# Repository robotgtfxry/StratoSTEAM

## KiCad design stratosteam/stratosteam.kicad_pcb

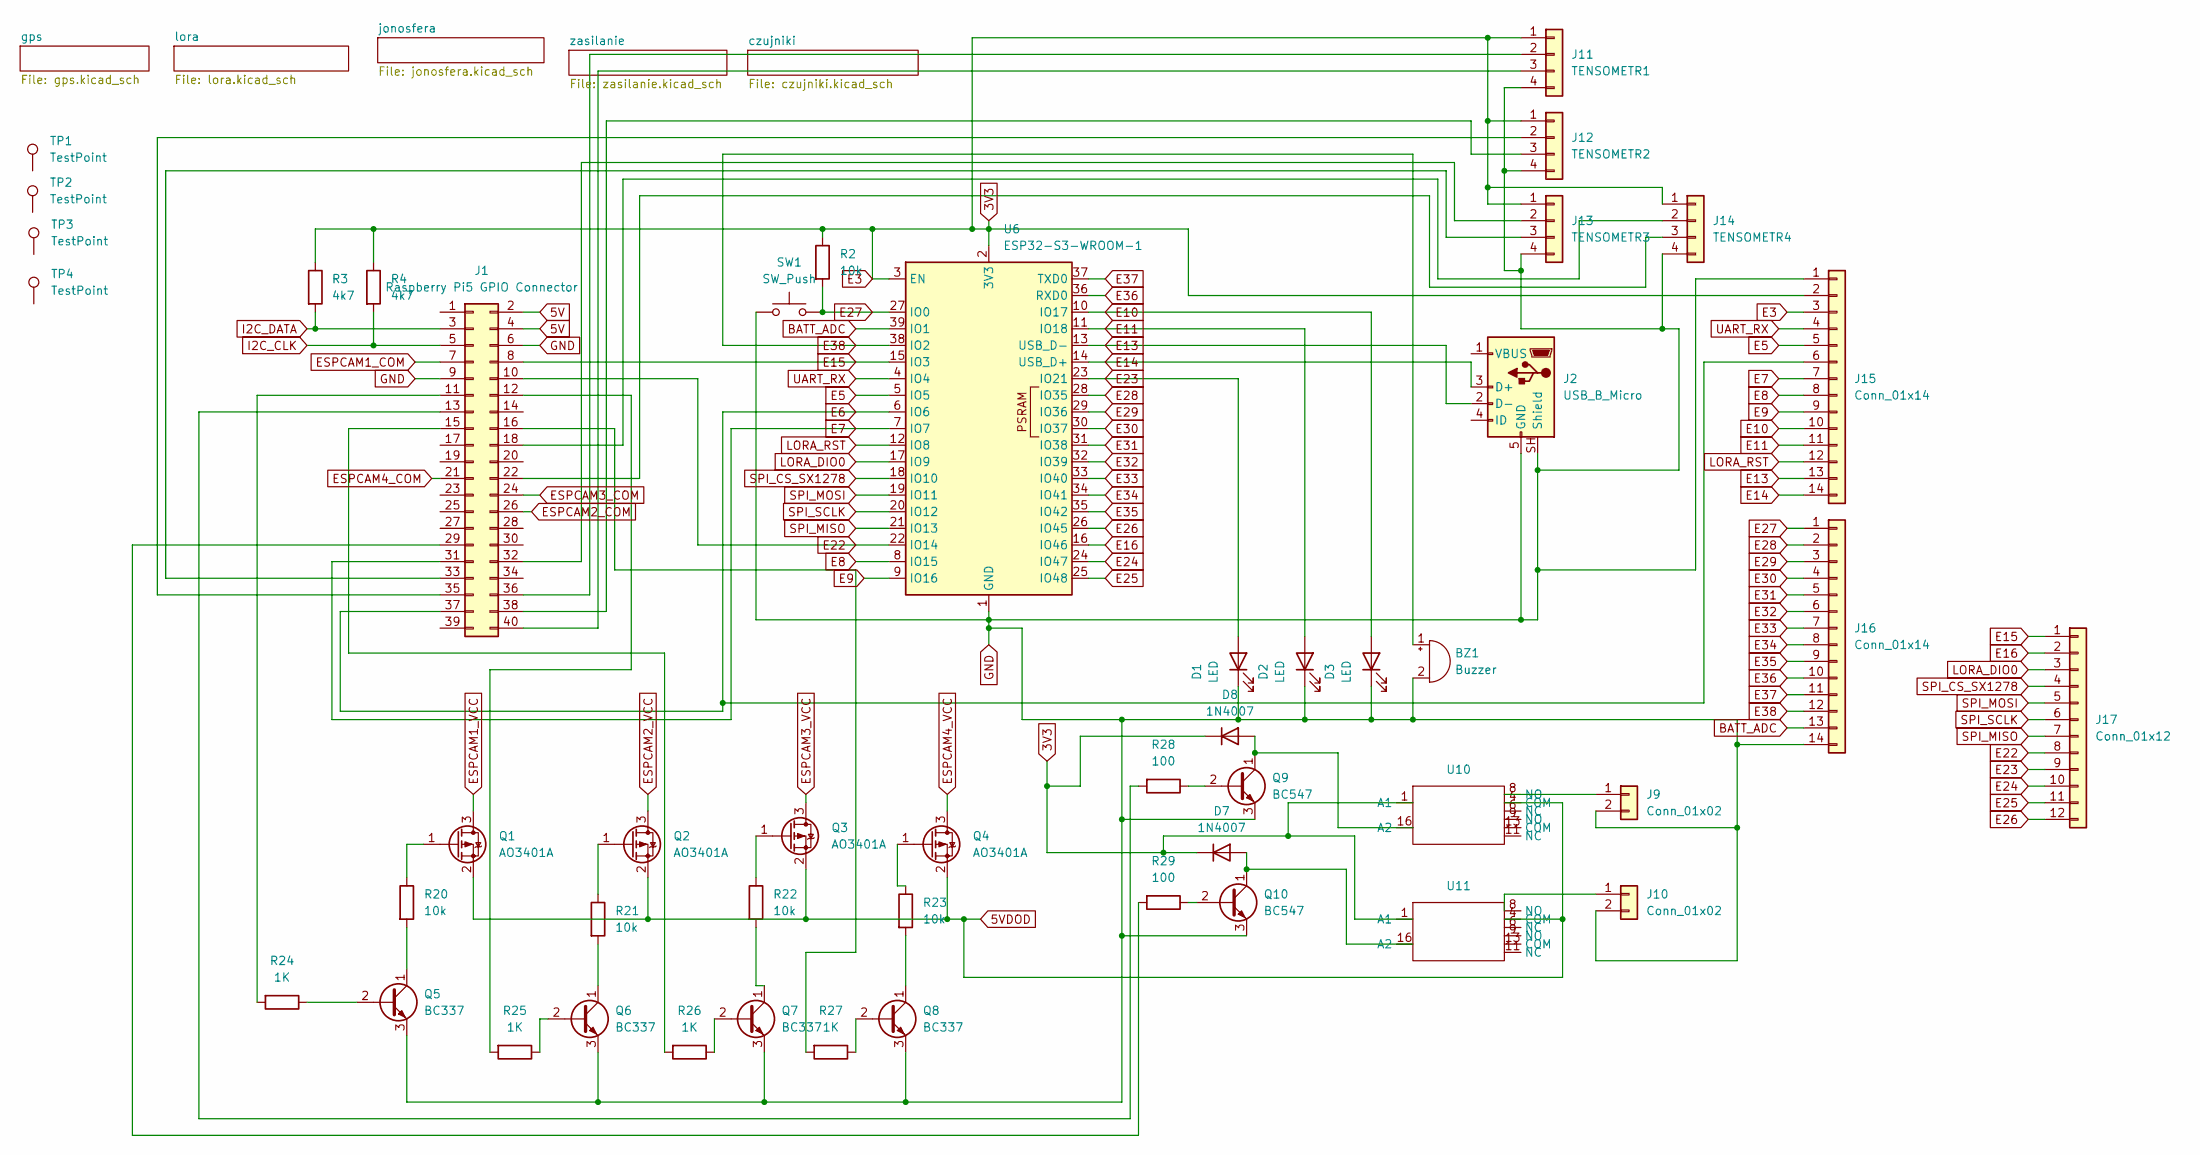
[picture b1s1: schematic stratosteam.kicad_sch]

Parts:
BZ1: Buzzer; Buzzer_12x9.5RM7.6
D1, D2, D3: LED; LED_D3.0mm
D7, D8: 1N4007; D_DO-41_SOD81_P10.16mm_Horizontal
J1: Raspberry Pi5 GPIO Connector; PinHeader_2x20_P2.54mm_Vertical
J2: USB_B_Micro; USB_Micro-B_Molex-105017-0001
J9, J10: Conn_01x02; JST_XH_B2B-XH-AM_1x02_P2.50mm_Vertical
J11: TENSOMETR1; JST_XH_B4B-XH-AM_1x04_P2.50mm_Vertical
J12: TENSOMETR2; JST_XH_B4B-XH-AM_1x04_P2.50mm_Vertical
J13: TENSOMETR3; JST_XH_B4B-XH-AM_1x04_P2.50mm_Vertical
J14: TENSOMETR4; JST_XH_B4B-XH-AM_1x04_P2.50mm_Vertical
J15, J16: Conn_01x14; PinHeader_1x14_P2.54mm_Vertical
J17: Conn_01x12; PinHeader_1x12_P2.54mm_Vertical
Q1, Q2, Q3, Q4: AO3401A; SOT-23_Handsoldering
Q5, Q6, Q7, Q8: BC337; TO-92_Inline
Q9, Q10: BC547; TO-92_Inline
R2: 10k; R_Axial_DIN0207_L6.3mm_D2.5mm_P15.24mm_Horizontal
R3, R4: 4k7; R_Axial_DIN0207_L6.3mm_D2.5mm_P15.24mm_Horizontal
R20, R21, R22, R23: 10k; R_0805_2012Metric_Pad1.20x1.40mm_HandSolder
R24, R25, R26, R27: 1K; R_0805_2012Metric_Pad1.20x1.40mm_HandSolder
R28, R29: 100; R_0805_2012Metric_Pad1.20x1.40mm_HandSolder
SW1: SW_Push; SW_DIP_SPSTx01_Slide_9.78x4.72mm_W7.62mm_P2.54mm
TP1, TP2, TP3, TP4: TestPoint; TestPoint_Loop_D3.80mm_Drill2.8mm
U6: ESP32-S3-WROOM-1
U10, U11: HJR1-2C SERIES

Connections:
3V3: D7.1 (K), D8.1 (K), J11.1, J12.1, J13.1, J14.1, J15.2, J15.3, R2.1, R3.1, R4.1, U6.2 (3V3), U6.3 (EN), U10.1 (A1), U11.1 (A1); also elsewhere on the board
5V: J1.2, J1.4; also elsewhere on the board
5VDOD: Q1.2 (S), Q2.2 (S), Q3.2 (S), Q4.2 (S), U10.4 (COM), U11.4 (COM); also elsewhere on the board
BAT-: BZ1.2 (-), D1.1 (K), D2.1 (K), D3.1 (K), J1.6, J1.9, J2.5 (GND), J2.SH (Shield), J9.2, J10.2, J11.4, J12.4, J13.4, J14.4, J15.1, J16.14, Q5.3 (E), Q6.3 (E), Q7.3 (E), Q8.3 (E), Q9.3 (E), Q10.3 (E), SW1.1, U6.1 (GND), U6.40 (GND), U6.41 (GND); also elsewhere on the board
BATT_ADC: J16.13, U6.39 (IO1); also elsewhere on the board
E5: J15.5, U6.5 (IO5)
E6: J1.37, J15.6, U6.6 (IO6); also elsewhere on the board
E7: J1.31, J15.7, U6.7 (IO7); also elsewhere on the board
E8: J15.8, U6.8 (IO15)
E9: J15.9, U6.9 (IO16)
E10: D3.2 (A), J15.10, U6.10 (IO17)
E11: D2.2 (A), J15.11, U6.11 (IO18)
E13: J2.2 (D-), J15.13, U6.13 (USB_D-)
E14: J2.3 (D+), J15.14, U6.14 (USB_D+)
E15: J1.8, J17.1, U6.15 (IO3); also elsewhere on the board
E16: J17.2, U6.16 (IO46)
E22: J1.10, J17.8, U6.22 (IO14); also elsewhere on the board
E23: D1.2 (A), J17.9, U6.23 (IO21)
E24: J17.10, U6.24 (IO47)
E25: J17.11, U6.25 (IO48)
E26: J17.12, U6.26 (IO45)
E27: J16.1, R2.2, SW1.2, U6.27 (IO0)
E28: J16.2, U6.28 (IO35)
E29: J16.3, U6.29 (IO36)
E30: J16.4, U6.30 (IO37)
E31: J16.5, U6.31 (IO38)
E32: J16.6, U6.32 (IO39)
E33: J16.7, U6.33 (IO40)
E34: J16.8, U6.34 (IO41)
E35: J16.9, U6.35 (IO42)
E36: J16.10, U6.36 (RXD0)
E37: J16.11, U6.37 (TXD0)
E38: BZ1.1 (+), J16.12, U6.38 (IO2)
ESPCAM1_COM: J1.7; also elsewhere on the board
ESPCAM1_VCC: Q1.3 (D); also elsewhere on the board
ESPCAM2_COM: J1.26; also elsewhere on the board
ESPCAM2_VCC: Q2.3 (D); also elsewhere on the board
ESPCAM3_COM: J1.24; also elsewhere on the board
ESPCAM3_VCC: Q3.3 (D); also elsewhere on the board
ESPCAM4_COM: J1.21; also elsewhere on the board
ESPCAM4_VCC: Q4.3 (D); also elsewhere on the board
I2C_CLK: J1.5, R4.2; also elsewhere on the board
I2C_DATA: J1.3, R3.2; also elsewhere on the board
LORA_DIO0: J17.3, U6.17 (IO9); also elsewhere on the board
LORA_RST: J15.12, U6.12 (IO8); also elsewhere on the board
unnamed: D7.2 (A), Q10.1 (C), U11.16 (A2)
unnamed: D8.2 (A), Q9.1 (C), U10.16 (A2)
unnamed 55: J1.11, R24.2; also elsewhere on the board
unnamed 56: J1.12, R25.2; also elsewhere on the board
unnamed 57: J1.13, R28.2; also elsewhere on the board
unnamed 58: J1.15, R26.2; also elsewhere on the board
unnamed 59: J1.16, R27.2; also elsewhere on the board
unnamed 60: J1.18, J14.2; also elsewhere on the board
unnamed 61: J1.22, J14.3; also elsewhere on the board
unnamed 62: J1.29, R29.2; also elsewhere on the board
unnamed 63: J1.32, J13.2; also elsewhere on the board
unnamed 64: J1.33, J13.3; also elsewhere on the board
unnamed 65: J1.35, J12.2; also elsewhere on the board
unnamed 66: J1.36, J11.2; also elsewhere on the board
unnamed 67: J1.38, J12.3; also elsewhere on the board
unnamed 68: J1.40, J11.3; also elsewhere on the board
unnamed: J9.1, U10.8 (NO)
unnamed: J10.1, U11.8 (NO)
unnamed: Q1.1 (G), R20.1
unnamed: Q2.1 (G), R21.1
unnamed: Q3.1 (G), R22.1
unnamed: Q4.1 (G), R23.1
unnamed: Q5.2 (B), R24.1
unnamed: Q5.1 (C), R20.2
unnamed: Q6.2 (B), R25.1
unnamed: Q6.1 (C), R21.2
unnamed: Q7.2 (B), R26.1
unnamed: Q7.1 (C), R22.2
unnamed: Q8.2 (B), R27.1
unnamed: Q8.1 (C), R23.2
unnamed: Q9.2 (B), R28.1
unnamed: Q10.2 (B), R29.1
SPI_CS_SX1278: J17.4, U6.18 (IO10); also elsewhere on the board
SPI_MISO: J17.7, U6.21 (IO13); also elsewhere on the board
SPI_MOSI: J17.5, U6.19 (IO11); also elsewhere on the board
SPI_SCLK: J17.6, U6.20 (IO12); also elsewhere on the board
UART_RX: J15.4, U6.4 (IO4); also elsewhere on the board

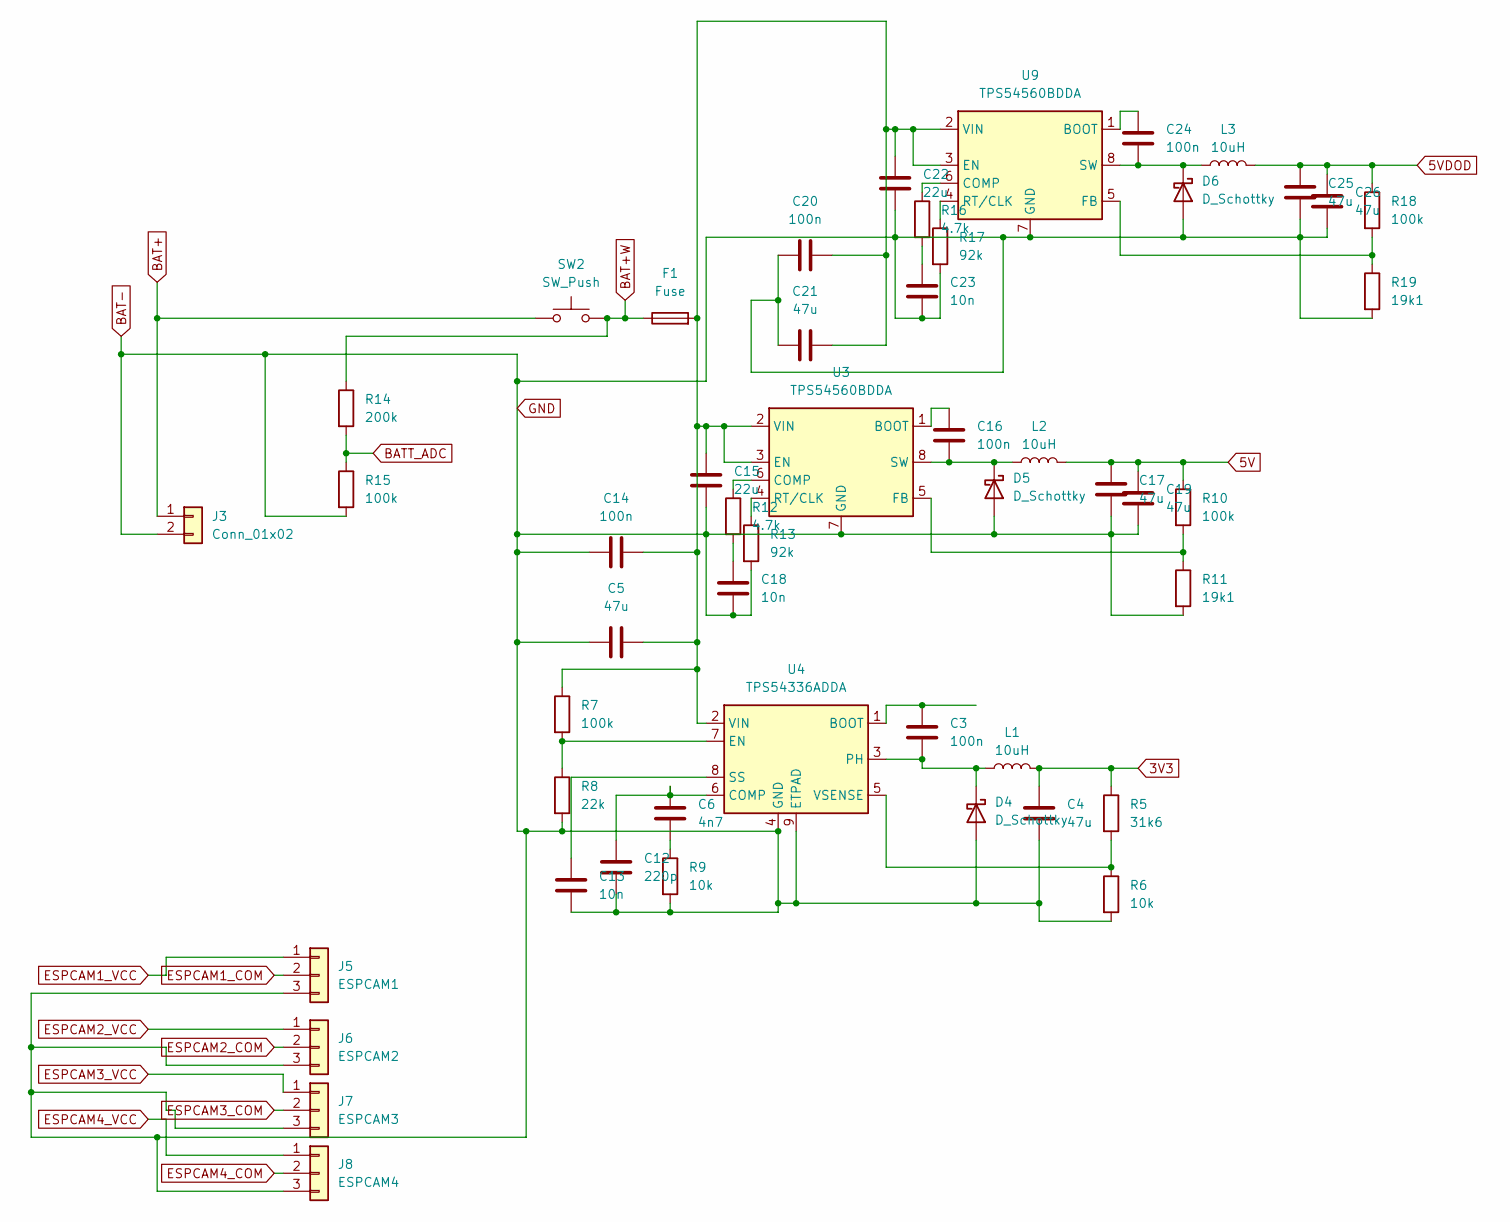
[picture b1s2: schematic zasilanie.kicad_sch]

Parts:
C3, C14, C16, C20, C24: 100n; C_0603_1608Metric_Pad1.08x0.95mm_HandSolder
C4, C17, C19, C25, C26: 47u; C_1210_3225Metric_Pad1.33x2.70mm_HandSolder
C5, C21: 47u; C_1206_3216Metric_Pad1.33x1.80mm_HandSolder
C6: 4n7; C_0603_1608Metric_Pad1.08x0.95mm_HandSolder
C12: 220p; C_0603_1608Metric_Pad1.08x0.95mm_HandSolder
C13, C18, C23: 10n; C_0603_1608Metric_Pad1.08x0.95mm_HandSolder
C15, C22: 22u; C_1206_3216Metric_Pad1.33x1.80mm_HandSolder
D4, D5, D6: D_Schottky; D_SMA
F1: Fuse; Fuseholder_Blade_ATO_Littelfuse_Pudenz_2_Pin
J3: Conn_01x02; SolderWire-2.5sqmm_1x02_P8.8mm_D2.4mm_OD4.4mm
J5: ESPCAM1; JST_XH_B3B-XH-A_1x03_P2.50mm_Vertical
J6: ESPCAM2; JST_XH_B3B-XH-A_1x03_P2.50mm_Vertical
J7: ESPCAM3; JST_XH_B3B-XH-A_1x03_P2.50mm_Vertical
J8: ESPCAM4; JST_XH_B3B-XH-A_1x03_P2.50mm_Vertical
L1, L2, L3: 10uH; L_12x12mm_H4.5mm
R5: 31k6; C_0603_1608Metric_Pad1.08x0.95mm_HandSolder
R6, R9: 10k; C_0603_1608Metric_Pad1.08x0.95mm_HandSolder
R7, R10, R15, R18: 100k; C_0603_1608Metric_Pad1.08x0.95mm_HandSolder
R8: 22k; C_0603_1608Metric_Pad1.08x0.95mm_HandSolder
R11, R19: 19k1; C_0603_1608Metric_Pad1.08x0.95mm_HandSolder
R12, R16: 4.7k; C_0603_1608Metric_Pad1.08x0.95mm_HandSolder
R13, R17: 92k; C_0603_1608Metric_Pad1.08x0.95mm_HandSolder
R14: 200k; C_0603_1608Metric_Pad1.08x0.95mm_HandSolder
SW2: SW_Push; SW_DIP_SPSTx01_Slide_9.78x4.72mm_W7.62mm_P2.54mm
U3, U9: TPS54560BDDA; Texas_R-PDSO-G8_EP2.95x4.9mm_Mask2.4x3.1mm_ThermalVias
U4: TPS54336ADDA; TI_SO-PowerPAD-8_ThermalVias

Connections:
3V3: C4.1, L1.2, R5.1; also elsewhere on the board
5V: C17.1, C19.1, L2.2, R10.1; also elsewhere on the board
5VDOD: C25.1, C26.1, L3.2, R18.1; also elsewhere on the board
BAT+: J3.1, SW2.1
BAT+W: F1.1, R14.1, SW2.2; also elsewhere on the board
BAT-: C4.2, C5.2, C12.2, C13.2, C14.1, C15.2, C17.2, C18.2, C19.2, C20.1, C21.2, C22.2, C23.2, C25.2, C26.2, D4.2 (A), D5.2 (A), D6.2 (A), J3.2, J5.3, J6.3, J7.3, J8.3, R6.2, R8.2, R9.2, R11.2, R13.2, R15.2, R17.2, R19.2, U3.7 (GND), U3.9 (GND), U4.4 (GND), U4.9 (ETPAD), U9.7 (GND), U9.9 (GND); also elsewhere on the board
BATT_ADC: R14.2, R15.1; also elsewhere on the board
ESPCAM1_COM: J5.2; also elsewhere on the board
ESPCAM1_VCC: J5.1; also elsewhere on the board
ESPCAM2_COM: J6.2; also elsewhere on the board
ESPCAM2_VCC: J6.1; also elsewhere on the board
ESPCAM3_COM: J7.2; also elsewhere on the board
ESPCAM3_VCC: J7.1; also elsewhere on the board
ESPCAM4_COM: J8.2; also elsewhere on the board
ESPCAM4_VCC: J8.1; also elsewhere on the board
unnamed: C6.2, R9.1
unnamed: C18.1, R12.2
unnamed: C23.1, R16.2
unnamed: C3.2, D4.1 (K), L1.1, U4.3 (PH)
unnamed: C16.2, D5.1 (K), L2.1, U3.8 (SW)
unnamed: C24.2, D6.1 (K), L3.1, U9.8 (SW)
unnamed: C16.1, U3.1 (BOOT)
unnamed: R12.1, U3.6 (COMP)
unnamed: C5.1, C14.2, C15.1, C20.2, C21.1, C22.1, F1.2, R7.1, U3.2 (VIN), U3.3 (EN), U4.2 (VIN), U9.2 (VIN), U9.3 (EN)
unnamed: R10.2, R11.1, U3.5 (FB)
unnamed: R13.1, U3.4 (RT/CLK)
unnamed: C3.1, U4.1 (BOOT)
unnamed: C6.1, C12.1, U4.6 (COMP)
unnamed: R7.2, R8.1, U4.7 (EN)
unnamed: C13.1, U4.8 (SS)
unnamed: R5.2, R6.1, U4.5 (VSENSE)
unnamed: C24.1, U9.1 (BOOT)
unnamed: R16.1, U9.6 (COMP)
unnamed: R18.2, R19.1, U9.5 (FB)
unnamed: R17.1, U9.4 (RT/CLK)

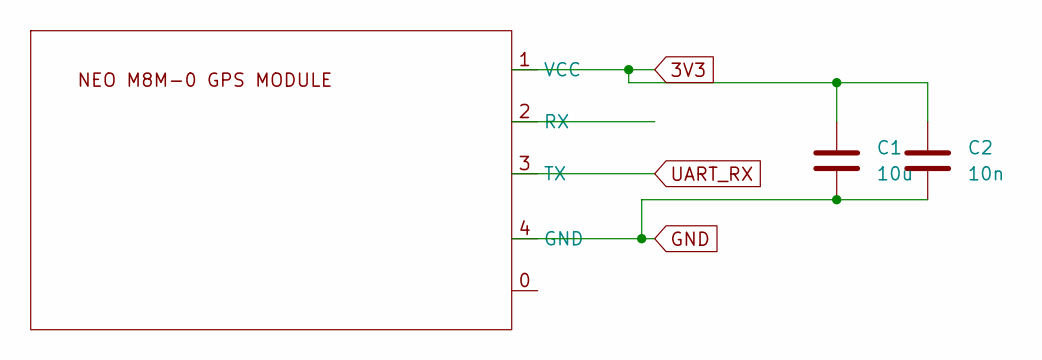
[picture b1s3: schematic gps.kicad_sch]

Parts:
C1: 10u; C_1210_3225Metric_Pad1.33x2.70mm_HandSolder
C2: 10n; C_1210_3225Metric_Pad1.33x2.70mm_HandSolder
U1: Untitled

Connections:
3V3: C1.1, C2.1, U1.1 (VCC); also elsewhere on the board
BAT-: C1.2, C2.2, U1.4 (GND); also elsewhere on the board
UART_RX: U1.3 (TX); also elsewhere on the board

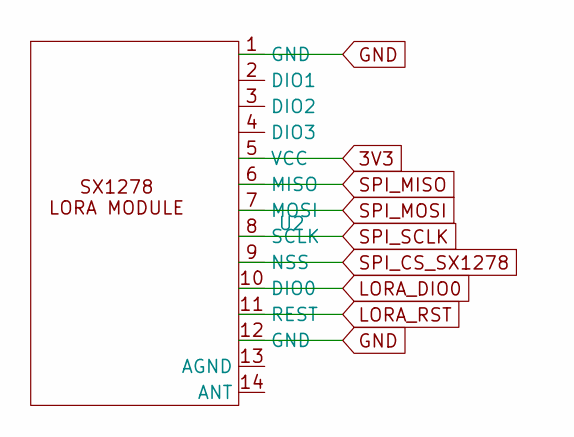
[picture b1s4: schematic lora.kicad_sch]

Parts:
U2: SX1278 MODULE

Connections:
3V3: U2.5 (VCC); also elsewhere on the board
BAT-: U2.1 (GND), U2.12 (GND); also elsewhere on the board
LORA_DIO0: U2.10 (DIO0); also elsewhere on the board
LORA_RST: U2.11 (REST); also elsewhere on the board
SPI_CS_SX1278: U2.9 (NSS); also elsewhere on the board
SPI_MISO: U2.6 (MISO); also elsewhere on the board
SPI_MOSI: U2.7 (MOSI); also elsewhere on the board
SPI_SCLK: U2.8 (SCLK); also elsewhere on the board

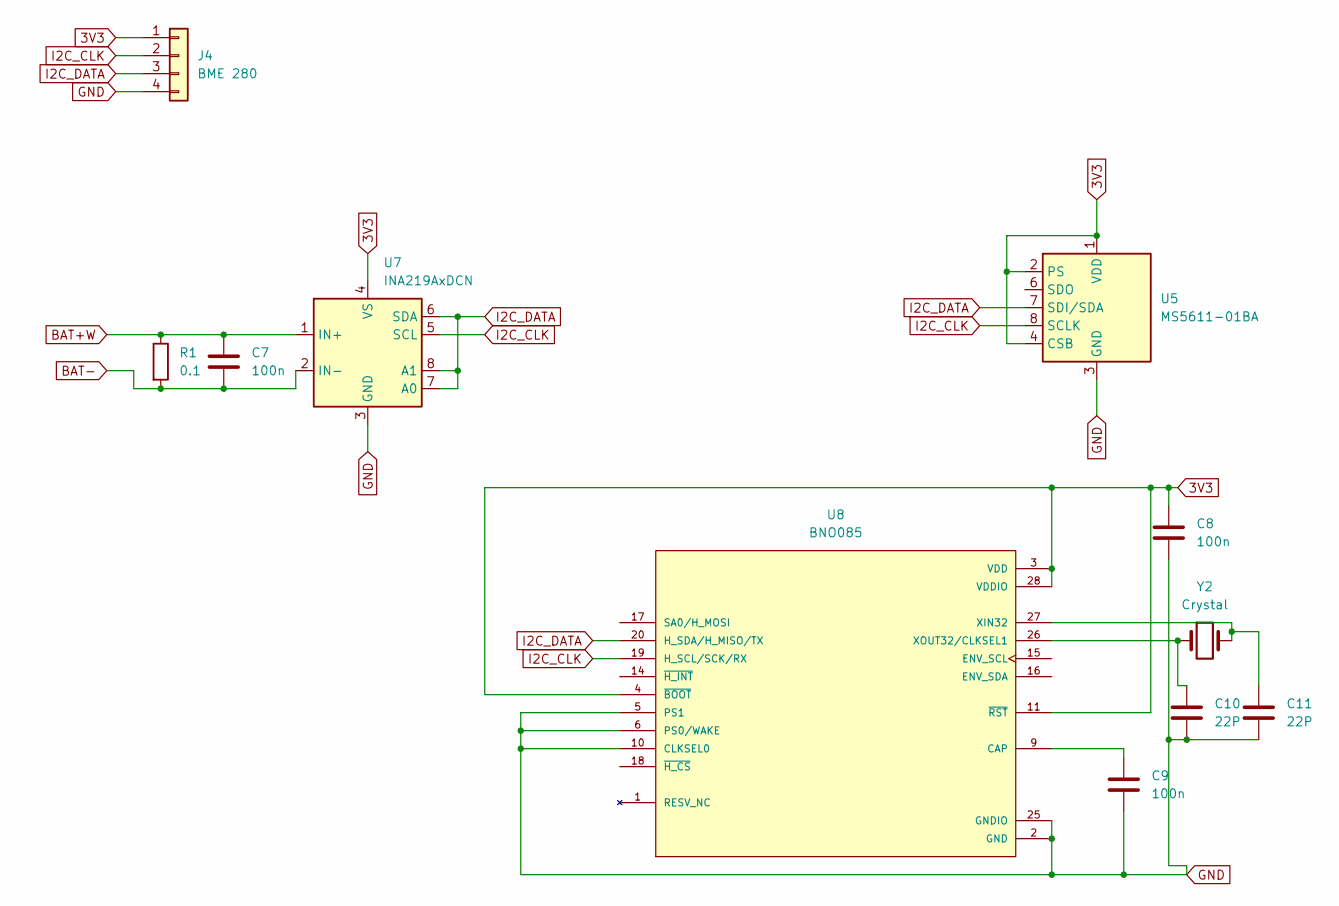
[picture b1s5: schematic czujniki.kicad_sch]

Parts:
C7, C8, C9: 100n; C_0805_2012Metric_Pad1.18x1.45mm_HandSolder
C10, C11: 22P; C_0805_2012Metric_Pad1.18x1.45mm_HandSolder
J4: BME 280; JST_EH_B4B-EH-A_1x04_P2.50mm_Vertical
R1: 0.1; R_2512_6332Metric_Pad1.40x3.35mm_HandSolder
U5: MS5611-01BA; LGA-8_3x5mm_P1.25mm
U7: INA219AxDCN; SOT-23-8
U8: BNO085; LGA-28_5.2x3.8mm_P0.5mm; PARTREV v1.17
Y2: Crystal; Crystal_SMD_3215-2Pin_3.2x1.5mm

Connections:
3V3: C8.1, J4.1, U5.1 (VDD), U5.2 (PS), U5.4 (CSB), U5.5 (CSB), U7.4 (VS), U8.3 (VDD), U8.4 (~BOOT), U8.11 (~RST), U8.28 (VDDIO); also elsewhere on the board
BAT+W: C7.1, R1.1, U7.1 (IN+); also elsewhere on the board
BAT-: C7.2, C8.2, C9.2, C10.2, C11.2, J4.4, R1.2, U5.3 (GND), U7.2 (IN-), U7.3 (GND), U8.2 (GND), U8.5 (PS1), U8.6 (PS0/WAKE), U8.10 (CLKSEL0), U8.25 (GNDIO); also elsewhere on the board
I2C_CLK: J4.2, U5.8 (SCLK), U7.5 (SCL), U8.19 (H_SCL/SCK/RX); also elsewhere on the board
I2C_DATA: J4.3, U5.7 (SDI/SDA), U7.6 (SDA), U7.7 (A0), U7.8 (A1), U8.20 (H_SDA/H_MISO/TX); also elsewhere on the board
unnamed: C9.1, U8.9 (CAP)
unnamed: C11.1, U8.27 (XIN32), Y2.2
unnamed: C10.1, U8.26 (XOUT32/CLKSEL1), Y2.1

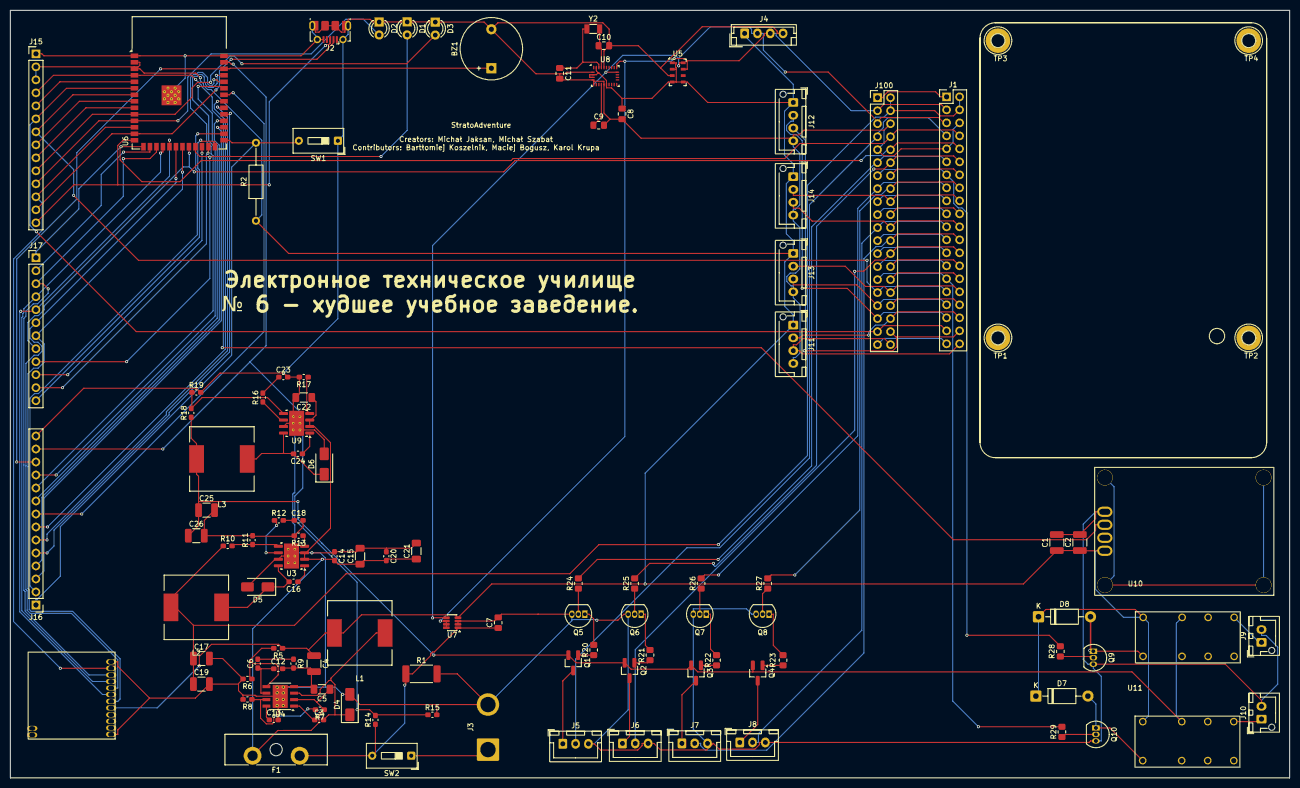
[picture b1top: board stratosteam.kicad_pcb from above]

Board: 2 copper layers, 250.0 x 150.0 mm, 112 parts (0 on the bottom side), 107 nets.

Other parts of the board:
J100: Raspberry Pi5 GPIO Connector; PinHeader_2x20_P2.54mm_Vertical

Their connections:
5V: J100.2, J100.4; also elsewhere on the board
BAT-: J100.6, J100.9; also elsewhere on the board
E6: J100.37; also elsewhere on the board
E7: J100.31; also elsewhere on the board
E15: J100.8; also elsewhere on the board
E22: J100.10; also elsewhere on the board
ESPCAM1_COM: J100.7; also elsewhere on the board
ESPCAM2_COM: J100.26; also elsewhere on the board
ESPCAM3_COM: J100.24; also elsewhere on the board
ESPCAM4_COM: J100.21; also elsewhere on the board
I2C_CLK: J100.5; also elsewhere on the board
I2C_DATA: J100.3; also elsewhere on the board
unnamed 55: J100.11; also elsewhere on the board
unnamed 56: J100.12; also elsewhere on the board
unnamed 57: J100.13; also elsewhere on the board
unnamed 58: J100.15; also elsewhere on the board
unnamed 59: J100.16; also elsewhere on the board
unnamed 60: J100.18; also elsewhere on the board
unnamed 61: J100.22; also elsewhere on the board
unnamed 62: J100.29; also elsewhere on the board
unnamed 63: J100.32; also elsewhere on the board
unnamed 64: J100.33; also elsewhere on the board
unnamed 65: J100.35; also elsewhere on the board
unnamed 66: J100.36; also elsewhere on the board
unnamed 67: J100.38; also elsewhere on the board
unnamed 68: J100.40; also elsewhere on the board

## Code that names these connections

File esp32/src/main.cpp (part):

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#define LORA_MOSI_PIN  11
#define LORA_MISO_PIN  13
#define LORA_CS_PIN    10
#define LORA_DIO0_PIN  9
#define LORA_RST_PIN   8
#define RPI_PWR_PIN    5
#define RPI_ALIVE_PIN  6
#define RPI_SHTDN_PIN  7
#define RPI_TX_PIN     14   // UART2 TX → RPi GPIO15 (RX)
#define BATT_ADC_PIN   1
#define BUZZER_PIN     2
#define LED_R_PIN      17
#define LED_G_PIN      18
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#define BATT_SAMPLES 16
float readBattAdc() {
    uint32_t mv = 0;
    for (int i = 0; i < BATT_SAMPLES; i++) mv += analogReadMilliVolts(BATT_ADC_PIN);
    float v = (mv / (float)BATT_SAMPLES) / 1000.0f * BATT_DIV_RATIO;
    return roundf(v * 100.0f) / 100.0f;
}
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
bool initLoRa() {
    SPI.begin(LORA_SCK_PIN, LORA_MISO_PIN, LORA_MOSI_PIN, LORA_CS_PIN);
    LoRa.setPins(LORA_CS_PIN, LORA_RST_PIN, LORA_DIO0_PIN);
    if (!LoRa.begin(LORA_FREQ)) return false;
    LoRa.setSpreadingFactor(LORA_SF);
    LoRa.setSignalBandwidth(LORA_BW);
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    pinMode(RPI_SHTDN_PIN, OUTPUT);
    pinMode(RPI_ALIVE_PIN, INPUT_PULLDOWN);   // niepodłączona linia nie może udawać ALIVE
    analogReadResolution(12);
    analogSetPinAttenuation(BATT_ADC_PIN, ADC_11db);
    digitalWrite(RPI_SHTDN_PIN, LOW);

    loraOk = initLoRa();
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
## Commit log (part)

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2026-05-21 PCB
    dodana druga przetwornica 5v
    uzupełnione niektóre footprinty
    częśc elementow przeniesiona ze schematu na pcb
2026-05-24 PCB
    dodane przekazniki, espcam, tensometry
2026-06-02 pcb
    prawie skonczone
2026-06-02 PCB
    chyba koniec
2026-06-02 pcb
    poprawione jeszcze raz
2026-06-10 pcb
    finalv1
2026-06-10 pcb
    finalv1.1
2026-06-12 xsx
    xsxsxsxsx
2026-06-12 pcb
    qwertyui
2026-06-12 pcb
    koniec
